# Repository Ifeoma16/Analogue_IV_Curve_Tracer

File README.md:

# Analogue I-V Curve Tracer Module

An fully analogue evaluation module designed to generate characteristic I-V (current-voltage) curves for Devices Under Test (DUT) [resistors, capacitors, inductors, diodes, NPN, NMOS] using standard oscilloscope X-Y plotting. 

See Analogue_IV_Curve_Tracer.pdf file for full project report / datasheet

## 🚀 Overview
Unlike digital curve tracers, this design uses zero microcontrollers. It utilizes a synchronized hardware-only topology:
* **Base/Gate Drive:** A CD4017B decade counter configured for a 5-step staircase waveform.
* **Collector/Drain Sweep:** An op-amp integrator generating a continuous triangle wave (approx. 9V pk-pk).
* **Power Management:** 9V battery-powered with an integrated charge pump (ICL7660) for negative rail generation and ESD/Reverse Polarity protection.

---

## ✨ Key Features
- **Standalone Operation:** No firmware to flash; purely analog circuitry.
- **Precision Layout:** 4-layer PCB ($SIG \rightarrow GND \rightarrow GND \rightarrow SIG$) optimized for low-noise microamp-level current steps.
- **Multi-Component Support:** Optimized for NPN Transistors, NMOS, Diodes (including schottky, zener etc), Inductors, Capacitors, Resistors.
- **Reactive Analysis:** Capable of visualizing phase-shift loops in Capacitors and Inductors.

---

## 🛠 Hardware Specifications
| Parameter | Typical Value |
| :--- | :--- |
| **Supply Voltage** | 9V (Alkaline Battery) |
| **Sweep Frequency** | ~100 Hz |
| **Base Current Steps** | 5 Steps (approx. 10µA increments) |
| **PCB Dimensions** | 60mm x 60mm |
| **Layer Count** | 4 Layers |

---

## 📈 Sample Traces
| NPN Transistor | Capacitor (100μF) | Inductor (1H) |
| :---: | :---: | :---: |
|  |  |  |

---

## 🔌 Setup & Usage
To visualize curves on your oscilloscope:
1. **Power:** Connect a 9V battery to the onboard holder.
2. **Probing:** - Connect one probe (this will be X-axis) to the part of your DUT that is connected to pin 1.
   - Connect a clamp probe (this will be Y-axis)  around the wire or pin that connects your Device Under Test (DUT) to pin 1
3. **Scope Settings:** - Enable **X-Y Mode**.
   - Use XY mode to plot current vs. voltage
   - Ensure both ground clips are tied to the circuit ground.

---

## 📂 Repository Structure
* `/curve_tracer`: Full project files, including schematic, layout and fabrication files.
* `/resources`: PDFs I used for learning more on curve tracers.
* `/images`: All images used in datasheet and PCB.

---

## ⚠️ Design Limitations
- **Polarity:** This version is optimized for NPN and NMOS devices. PNP/PMOS devices will result in mirrored/inverted plots.
- **Power Dissipation:** Limited by the sourcing capability of the TL072H op-amps and the 1kΩ sense resistor.

---

## 🥚 Easter Egg
Look closely at the silkscreen: the module features **Usain Bolt**. Why? 

## 📜 References & Acknowledgments
Detailed resources used during the design phase (MIT reports, Op-amp integrator theory, etc.) are archived in the `/resources` folder.

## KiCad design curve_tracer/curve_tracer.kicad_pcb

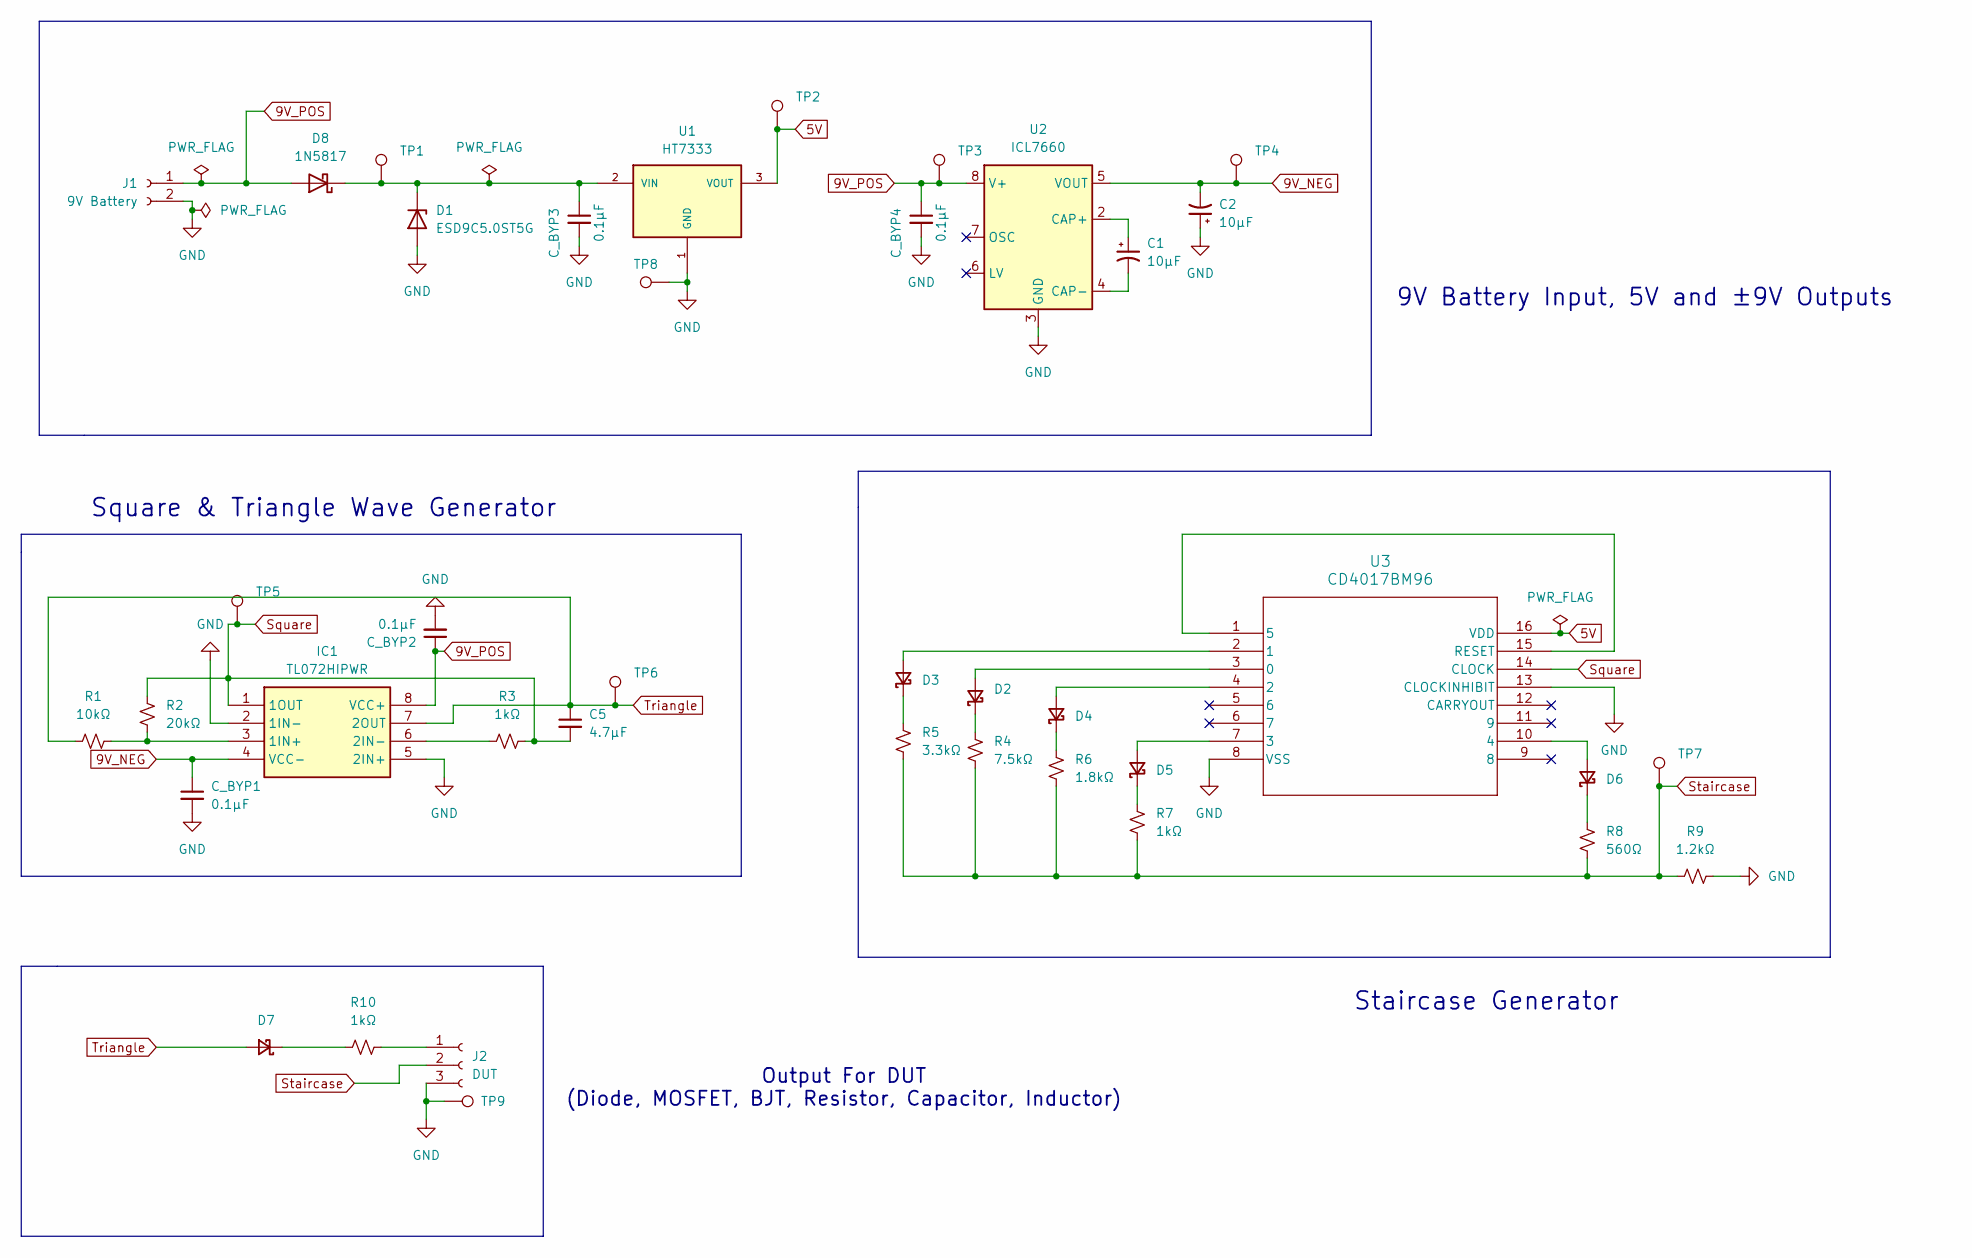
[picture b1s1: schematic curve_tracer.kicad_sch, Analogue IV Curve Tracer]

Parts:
C1, C2: 10μF; CP_Elec_4x5.8
C5: 4.7μF; C_0805_2012Metric
C_BYP1, C_BYP2, C_BYP3, C_BYP4: 0.1μF; C_0603_1608Metric
D1: ESD9C5.0ST5G; D_SOD-923
D2, D3, D4, D5, D6, D7: D_Schottky_Small; D_SOD-323
D8: 1N5817; D_SOD-123
IC1: TL072HIPWR; SOP65P640X120-8N; Manufacturer_Part_Number TL072HIPWR; Mouser Part Number 595-TL072HIPWR
J1: 9V Battery; BatteryHolder_MPD_BA9VPC_1xPP3
J2: DUT; PinSocket_1x03_P2.54mm_Vertical
R1: 10kΩ; R_0603_1608Metric
R2: 20kΩ; R_0603_1608Metric
R3, R7: 1kΩ; R_0603_1608Metric
R4: 7.5kΩ; R_0603_1608Metric
R5: 3.3kΩ; R_0603_1608Metric
R6: 1.8kΩ; R_0603_1608Metric
R8: 560Ω; R_0603_1608Metric
R9: 1.2kΩ; R_0603_1608Metric
R10: 1kΩ; R_Axial_DIN0207_L6.3mm_D2.5mm_P7.62mm_Horizontal
TP1, TP2, TP3, TP4, TP5, TP6, TP7, TP8, TP9: TestPoint; TestPoint_Loop_D2.50mm_Drill1.0mm_LowProfile
U1: HT7333; IC_HT7333; PARTREV 1.80
U2: ICL7660; SOIC8_4X5_INR
U3: CD4017BM96; D16

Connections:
5V: TP2.1 (1_1), U1.3 (VOUT), U3.16 (VDD)
9V_NEG: C2.2, C_BYP1.1, IC1.4 (VCC-), TP4.1 (1_1), U2.5 (VOUT)
9V_POS: C_BYP2.1, C_BYP4.1, D8.2 (A), IC1.8 (VCC+), J1.1, TP3.1 (1_1), U2.8 (V+)
GND: C2.1, C_BYP1.2, C_BYP2.2, C_BYP3.2, C_BYP4.2, D1.2 (A), IC1.2 (1IN-), IC1.5 (2IN+), J1.2, J2.3, R9.1, TP8.1 (1_1), TP9.1 (1_1), U1.1 (GND), U2.3 (GND), U3.8 (VSS), U3.13 (CLOCKINHIBIT)
unnamed: C_BYP3.1, D1.1 (K), D8.1 (K), TP1.1 (1_1), U1.2 (VIN)
unnamed: D2.2 (A), U3.3 (0)
unnamed: D2.1 (K), R4.2
unnamed: D3.2 (A), U3.2 (1)
unnamed: D3.1 (K), R5.2
unnamed: D4.2 (A), U3.4 (2)
unnamed: D4.1 (K), R6.2
unnamed: D5.2 (A), U3.7 (3)
unnamed: D5.1 (K), R7.2
unnamed: D6.2 (A), U3.10 (4)
unnamed: D6.1 (K), R8.2
unnamed: D7.1 (K), R10.1
unnamed: IC1.3 (1IN+), R1.2, R2.1
unnamed: IC1.6 (2IN-), R3.1
unnamed: J2.1, R10.2
unnamed: C1.1, U2.2 (CAP+)
unnamed: C1.2, U2.4 (CAP-)
unnamed: U3.1 (5), U3.15 (RESET)
Square: C5.2, IC1.1 (1OUT), R2.2, R3.2, TP5.1 (1_1), U3.14 (CLOCK)
Staircase: J2.2, R4.1, R5.1, R6.1, R7.1, R8.1, R9.2, TP7.1 (1_1)
Triangle: C5.1, D7.2 (A), IC1.7 (2OUT), R1.1, TP6.1 (1_1)

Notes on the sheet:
Square & Triangle Wave Generator
Staircase Generator
9V Battery Input, 5V and ±9V Outputs
Output For DUT (Diode, MOSFET, BJT, Resistor, Capacitor, Inductor)

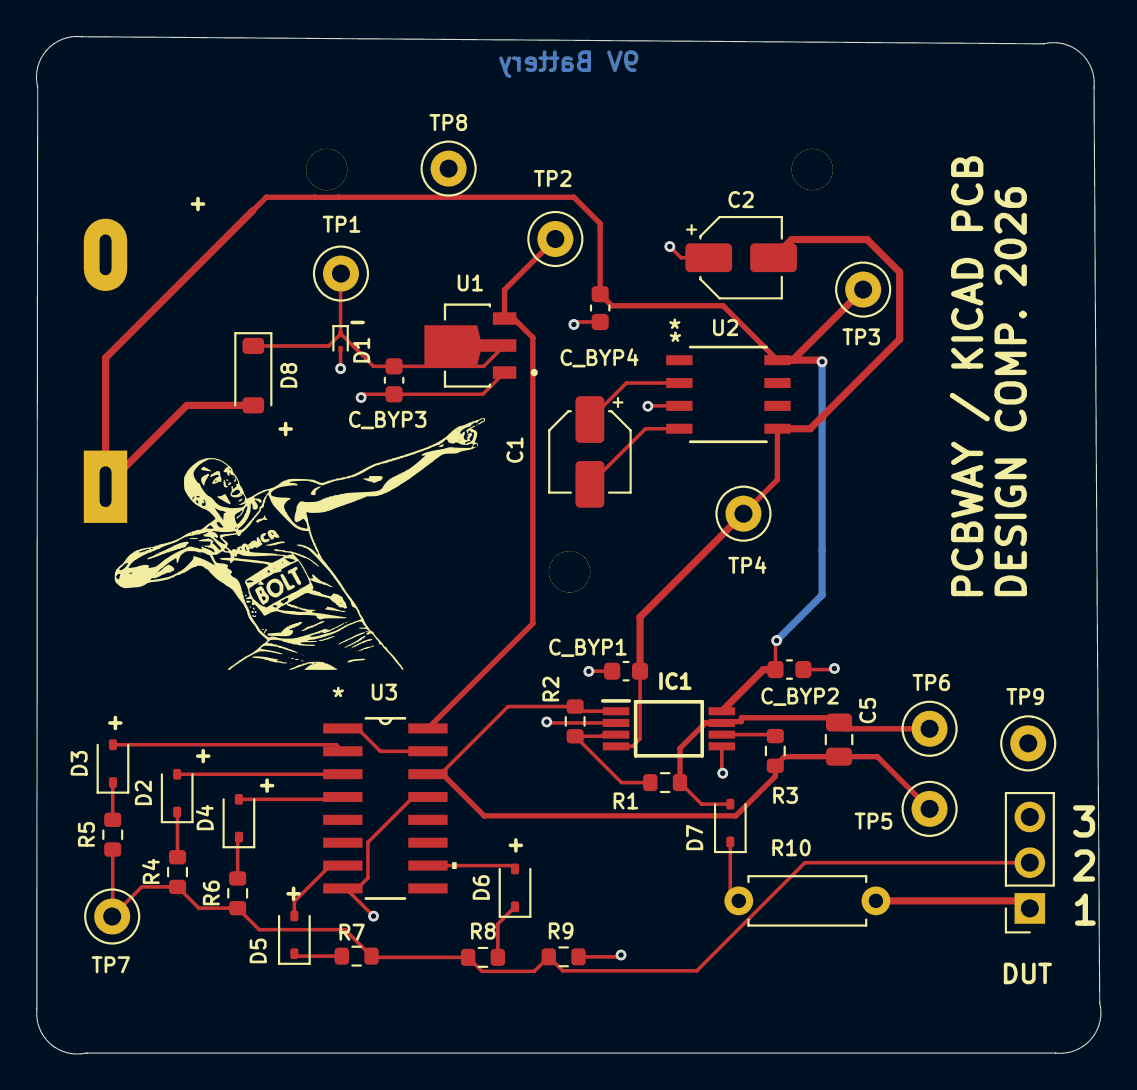
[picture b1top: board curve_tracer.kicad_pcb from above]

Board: 4 copper layers, 59.1 x 56.5 mm, 40 parts (1 on the bottom side), 25 nets.

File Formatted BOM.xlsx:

| Reference | Qty | Value | MFN | Unit Price | Link | Footprint
 | C1,C2 | 2 | 10µF | 865080340001 | 0.18 | 865080340001 | Capacitor_SMD:CP_Elec_4x5.8
 | C_BYP1,C_BYP2,C_BYP3,C_BYP4 | 4 | 0.1µF | C0603C104K4RACTU | 0.1 | C0603C104K4RACTU | Capacitor_SMD:C_0402_1005Metric
 | C5 | 1 | 4.7µF | HRE CSA0805X7R475K160MT | 1.89E-2 | HRE CSA0805X7R475K160MT | Capacitor_SMD:C_0805_2012Metric
 | D1 | 1 | ESD9C5.0ST5G | ESD9C5.0ST5G | 0.3 | ESD9C5.0ST5G | Diode_SMD:D_SOD-923
 | D2,D3,D4,D5,D6,D7 | 6 | D_Schottky_Small | CUS15S30,H3F | 0.34 | CUS15S30,H3F | Diode_SMD:D_SOD-323
 | IC1 | 1 | TL072HIPWR | TL072HIPWR | 0.31 | TL072H | TL072HIPWR:SOP65P640X120-8N
 | J1 | 1 | 9V Battery | BA9VPC | 2.5 | BA9VPC | Battery:BatteryHolder_MPD_BA9VPC_1xPP3
 | J2 | 1 | DUT | Chanzon Pin Header Strip | 0.14000000000000001 | Amazon | Connector_PinSocket_2.54mm:PinSocket_1x03_P2.54mm_Vertical
 | R1 | 1 | 10kΩ | RCS060310K0FKEA | 0.14000000000000001 | RCS060310K0FKEA | Resistor_SMD:R_0603_1608Metric
 | R2 | 1 | 20kΩ | RCS060320K0FKEA | 0.14000000000000001 | RCS060320K0FKEA | Resistor_SMD:R_0603_1608Metric
 | R3,R7 | 2 | 1kΩ | SG73P1JTTD1001F | 0.12 | SG73P1JTTD1001F | Resistor_SMD:R_0603_1608Metric
 | R4 | 1 | 7.5kΩ | RCS06037K50FKEA | 0.14000000000000001 | RCS06037K50FKEA | Resistor_SMD:R_0603_1608Metric
 | R5 | 1 | 3.3kΩ | RCS06033K30FKEA | 0.14000000000000001 | RCS06033K30FKEA | Resistor_SMD:R_0603_1608Metric
 | R6 | 1 | 1.8kΩ | RCS06031K80FKEA | 0.14000000000000001 | RCS06031K80FKEA | Resistor_SMD:R_0603_1608Metric
 | R8 | 1 | 560Ω | RCS0603560RFKEA | 0.14000000000000001 | RCS0603560RFKEA | Resistor_SMD:R_0603_1608Metric
 | R9 | 1 | 1.2kΩ | RCS06031K20FKEA | 0.13 | RCS06031K20FKEA | Resistor_SMD:R_0603_1608Metric
 | R10 | 1 | 1kΩ | MFR50SFTE52-1K | 0.1 | MFR50SFTE52-1K | Resistor_THT:R_Axial_DIN0207_L6.3mm_D2.5mm_P7.62mm_Horizontal
 | TP1,TP2,TP3,TP4,TP5,TP6,TP7,TP8,TP9 | 9 | TestPoint | Comimark | 6.5000000000000002E-2 | Amazon | TestPoint:TestPoint_Loop_D2.50mm_Drill1.0mm_LowProfile
 | D8 | 1 | 1N5817 | 1N5817W | 0.1 | 1N5817W | Diode_SMD:D_SOD-123
 | U1 | 1 | HT7350-A | HT7350-A | 0.42 | HT7350-A | Package_TO_SOT_SMD:SOT-223-3_TabPin2
 | U2 | 1 | ICL7660SCBAZ-T | ICL7660SCBAZ-T | 2.71 | ICL7660SCBAZ-T | Custom_miscellaneous_v10:ICL7660
 | U3 | 1 | CD4017BM96 | CD4017BM96 | 0.69 | CD4017B | CD4017BM96:D16
 |  |  |  | Component Total: | 11.883899999999999
 |  |  |  | PCBWay Quote (No PCBA) | 5.2 | Per Board
 |  |  |  | PCBWay Quote (With PCBA) | 11 | Per Board
 |  |  |  | Grand Total (No PCBA): | 17.0839
 |  |  |  | Grand Total (With PCBA): | 28.967799999999997

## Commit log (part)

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2026-04-28 Formatting repo
